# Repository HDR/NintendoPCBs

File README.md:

# [Make sure you read the License before downloading anything!](https://github.com/HDR/NintendoPCBs/blob/master/LICENSE)

# Please note that these boards can only be used to fix broken games, they can not be used for piracy/bootleg games

**All boards should be ordered in 0.8mm thickness with ENIG, Do not order in 1.6mm thickness or HASL!**

**AGB-E02-20:**

**AGB-E05-01:**

**DMG-KFDN-01:**

See the [Nintendo Board Scans](https://github.com/HDR/Nintendo_Board_Scans) for more.

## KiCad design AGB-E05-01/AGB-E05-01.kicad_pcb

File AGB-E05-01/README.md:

# AGB-E05-01

Intended as a replacement for Games like Emerald

## BOM
| **Designator** | **Part**                              |
|:-----------:|:-------------------------------------------------------------:|
| C1,C2,C3,C4 |                           100nF 0402                          |
|          C5 |            4pF or 10pF 0402 (depends on the board)            |
|    R1,R2,R3 |                          Unpopulated                          |
|    R4,R5,R9 |                            10K 0402                           |
|       R6,R7 |                           100K 0402                           |
|          R8 |                            1K 0402                            |
| R10         | 2K Resistor 0603 or 1uF Capacitor 0603 (depends on the board) |

### Images

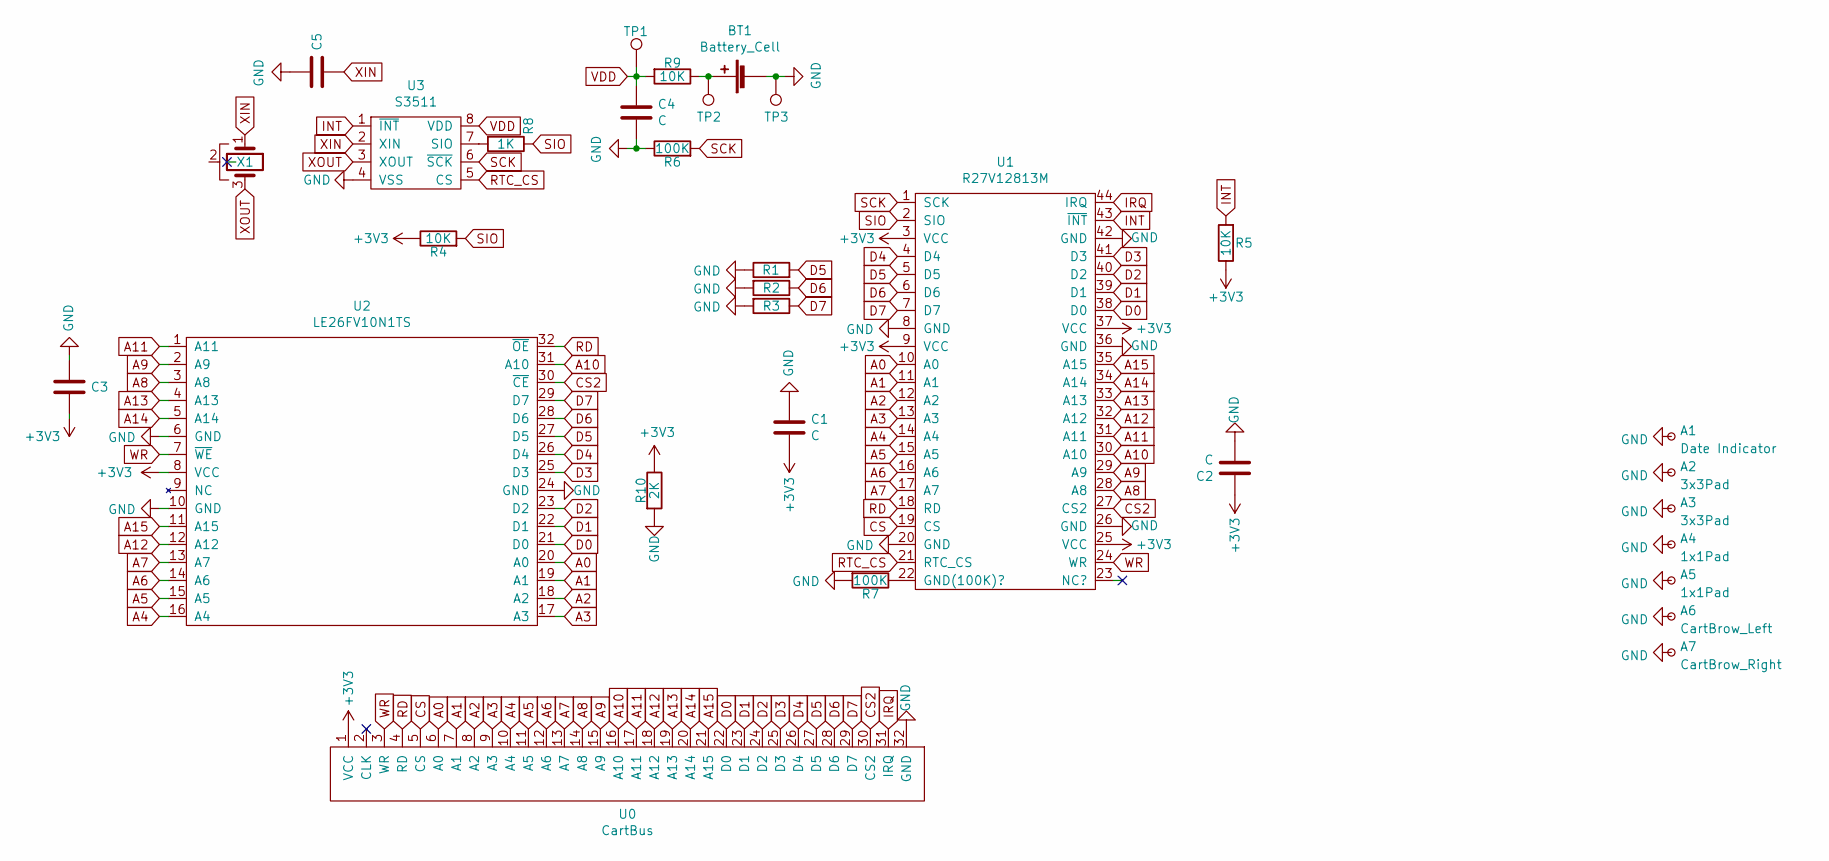
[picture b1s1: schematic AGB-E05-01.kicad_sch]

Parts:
A1: Date Indicator; 05 May
A2, A3: 3x3Pad; 3x3mm_Pad
A4, A5: 1x1Pad; 1x1mm_Pad
A6: CartBrow_Left; AGB-Cartbrow_Left
A7: CartBrow_Right; AGB-Cartbrow_Right
BT1: Battery_Cell; AGB-CR1616
C1, C2, C3, C4, C5: C; AGB-C_0402
R1, R2, R3: NC; AGB-R-0603_OPT
R4, R5, R9: 10K; AGB-R_0402
R6, R7: 100K; AGB-R_0402
R8: 1K; AGB-R_0402
R10: 2K; AGB-R-0603
TP1, TP2: TestPoint; AGB-Testpoint
TP3: TestPoint; AGB-Testpoint_Ground
U0: CartBus; AGB_Cartridge
U1: R27V12813M; AGB-TSOP-II-44_10.16x18.41mm_P0.8mm
U2: LE26FV10N1TS; AGB-TSOP-I-32
U3: S3511; AGB-SSOP8
X1: Crystal_GND2; AGB-Crystal

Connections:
+3V3: C1.1, C2.2, C3.1, R4.1, R5.1, R10.1, U0.1 (VCC), U1.3 (VCC), U1.9 (VCC), U1.25 (VCC), U1.37 (VCC), U2.8 (VCC)
A0: U0.6 (A0), U1.10 (A0), U2.20 (A0)
A1: U0.7 (A1), U1.11 (A1), U2.19 (A1)
A2: U0.8 (A2), U1.12 (A2), U2.18 (A2)
A3: U0.9 (A3), U1.13 (A3), U2.17 (A3)
A4: U0.10 (A4), U1.14 (A4), U2.16 (A4)
A5: U0.11 (A5), U1.15 (A5), U2.15 (A5)
A6: U0.12 (A6), U1.16 (A6), U2.14 (A6)
A7: U0.13 (A7), U1.17 (A7), U2.13 (A7)
A8: U0.14 (A8), U1.28 (A8), U2.3 (A8)
A9: U0.15 (A9), U1.29 (A9), U2.2 (A9)
A10: U0.16 (A10), U1.30 (A10), U2.31 (A10)
A11: U0.17 (A11), U1.31 (A11), U2.1 (A11)
A12: U0.18 (A12), U1.32 (A12), U2.12 (A12)
A13: U0.19 (A13), U1.33 (A13), U2.4 (A13)
A14: U0.20 (A14), U1.34 (A14), U2.5 (A14)
A15: U0.21 (A15), U1.35 (A15), U2.11 (A15)
CS: U0.5 (CS), U1.19 (CS)
CS2: U0.30 (CS2), U1.27 (CS2), U2.30 (~CE)
D0: U0.22 (D0), U1.38 (D0), U2.21 (D0)
D1: U0.23 (D1), U1.39 (D1), U2.22 (D1)
D2: U0.24 (D2), U1.40 (D2), U2.23 (D2)
D3: U0.25 (D3), U1.41 (D3), U2.25 (D3)
D4: U0.26 (D4), U1.4 (D4), U2.26 (D4)
D5: R1.2, U0.27 (D5), U1.5 (D5), U2.27 (D5)
D6: R2.1, U0.28 (D6), U1.6 (D6), U2.28 (D6)
D7: R3.1, U0.29 (D7), U1.7 (D7), U2.29 (D7)
GND: A1.1, A2.1, A3.1, A4.1, A5.1, A6.1, A7.1, BT1.2 (-), C1.2, C2.1, C3.2, C4.1, C5.1, R1.1, R2.2, R3.2, R6.1, R7.2, R10.2, TP3.1, U0.32 (GND), U1.8 (GND), U1.20 (GND), U1.26 (GND), U1.36 (GND), U1.42 (GND), U2.6 (GND), U2.10 (GND), U2.24 (GND), U3.4 (VSS); also elsewhere on the board
INT: R5.2, U1.43 (~INT), U3.1 (~INT)
IRQ: U0.31 (IRQ), U1.44 (IRQ)
unnamed: BT1.1 (+), R9.1, TP2.1
unnamed: R7.1, U1.22 (GND(100K)?)
unnamed: R8.2, U3.7 (SIO)
RD: U0.4 (RD), U1.18 (RD), U2.32 (~OE)
RTC_CS: U1.21 (RTC_CS), U3.5 (CS)
SCK: R6.2, U1.1 (SCK), U3.6 (~SCK)
SIO: R4.2, R8.1, U1.2 (SIO)
VDD: C4.2, R9.2, TP1.1, U3.8 (VDD)
WR: U0.3 (WR), U1.24 (WR), U2.7 (~WE)
XIN: C5.2, U3.2 (XIN), X1.1
XOUT: U3.3 (XOUT), X1.3

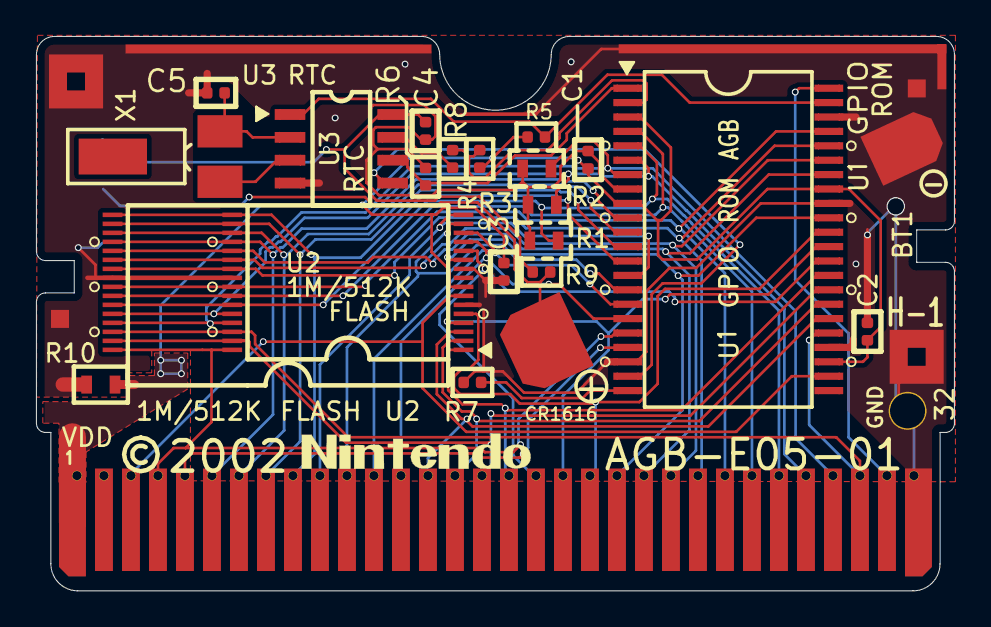
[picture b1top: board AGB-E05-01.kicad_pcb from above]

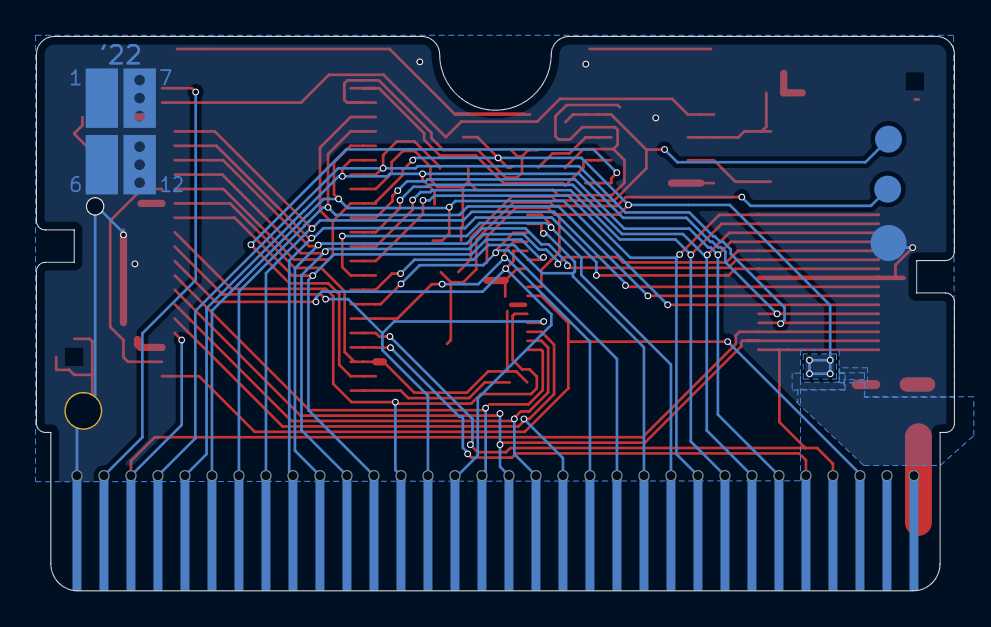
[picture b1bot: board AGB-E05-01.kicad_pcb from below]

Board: 2 copper layers, 51.0 x 30.8 mm, 36 parts (7 on the bottom side), 41 nets.

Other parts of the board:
G1: Nintendo Logo; Nintendo-GBA-Logo
PlatedHole1: MountingHole; TestPoint_Plated_Hole_D2.0mm
kibuzzard-62A1ACD3: G***; kibuzzard-62A1ACD3
kibuzzard-62A1AD16: G***; kibuzzard-62A1AD16
kibuzzard-62A1AD21: G***; kibuzzard-62A1AD21

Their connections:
GND: PlatedHole1.1; also elsewhere on the board

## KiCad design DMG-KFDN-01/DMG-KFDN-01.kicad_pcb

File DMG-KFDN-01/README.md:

# DMG-KFDN-01

Will be replaced with a better version in the coming weeks, please wait until then.

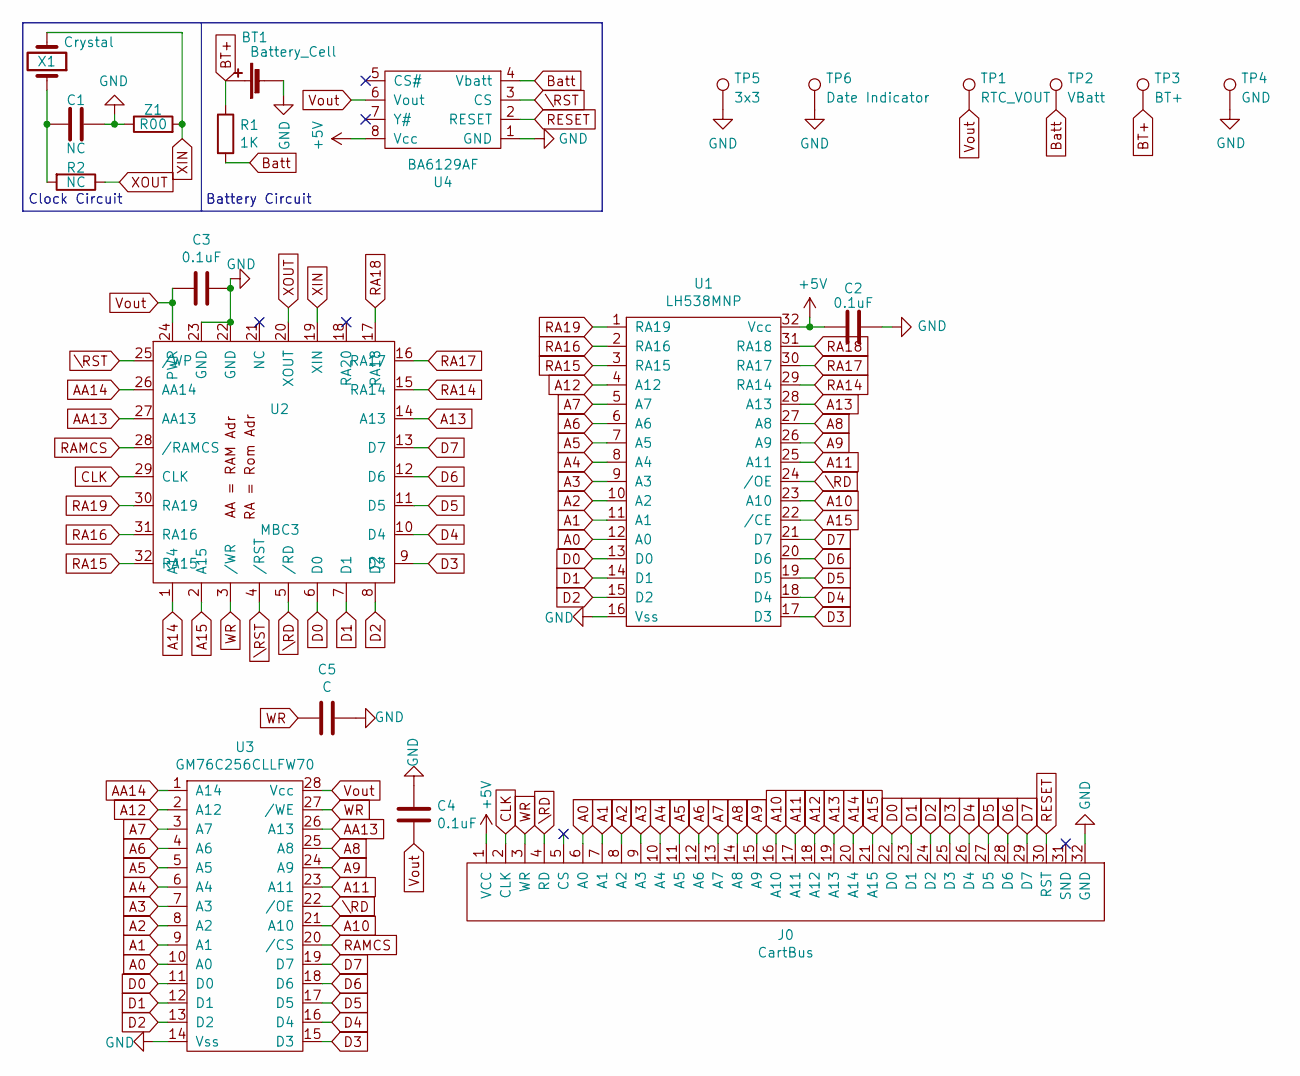
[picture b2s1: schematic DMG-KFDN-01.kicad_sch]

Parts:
BT1: Battery_Cell; CR2025_Tabbed
C1: NC; C_0805_2012Metric
C2, C3, C4: 0.1uF; C_0805_2012Metric
C5: C; C_0805_2012Metric
J0: CartBus; GB_Cartridge_Front_Only
R1: 1K; R_0805_2012Metric
R2: NC; R_0805_2012Metric
TP1: RTC_VOUT; GameBoy_Testpoint
TP2: VBatt; GameBoy_Testpoint
TP3: BT+; GameBoy_Testpoint
TP4: GND; GameBoy_Testpoint
TP5: 3x3; 3x3mm_Pad
TP6: Date Indicator; 12 December
U1: LH538MNP; SSOP-32_11.305x20.495mm_P1.27mm
U2: MBC3; LQFP-32_7x7mm_P0.8mm
U3: GM76C256CLLFW70; SOIC-28W_7.5x17.9mm_P1.27mm
U4: BA6129AF; SOIC-8_3.9x4.9mm_P1.27mm
X1: Crystal; Resonator_SMD_muRata_CDSCB-2pin_4.5x2.0mm_HandSoldering
Z1: R00; R_0805_2012Metric

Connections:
+5V: C2.1, J0.1 (VCC), U1.32 (Vcc), U4.8 (Vcc)
A0: J0.6 (A0), U1.12 (A0), U3.10 (A0)
A1: J0.7 (A1), U1.11 (A1), U3.9 (A1)
A2: J0.8 (A2), U1.10 (A2), U3.8 (A2)
A3: J0.9 (A3), U1.9 (A3), U3.7 (A3)
A4: J0.10 (A4), U1.8 (A4), U3.6 (A4)
A5: J0.11 (A5), U1.7 (A5), U3.5 (A5)
A6: J0.12 (A6), U1.6 (A6), U3.4 (A6)
A7: J0.13 (A7), U1.5 (A7), U3.3 (A7)
A8: J0.14 (A8), U1.27 (A8), U3.25 (A8)
A9: J0.15 (A9), U1.26 (A9), U3.24 (A9)
A10: J0.16 (A10), U1.23 (A10), U3.21 (A10)
A11: J0.17 (A11), U1.25 (A11), U3.23 (A11)
A12: J0.18 (A12), U1.4 (A12), U3.2 (A12)
A13: J0.19 (A13), U1.28 (A13), U2.14 (A13)
A14: J0.20 (A14), U2.1 (A14)
A15: J0.21 (A15), U1.22 (/CE), U2.2 (A15)
AA13: U2.27 (AA13), U3.26 (A13)
AA14: U2.26 (AA14), U3.1 (A14)
BT+: BT1.1 (+), R1.1, TP3.1; also elsewhere on the board
Batt: R1.2, TP2.1, U4.4 (Vbatt)
CLK: J0.2 (CLK~), U2.29 (CLK)
D0: J0.22 (D0), U1.13 (D0), U2.6 (D0), U3.11 (D0)
D1: J0.23 (D1), U1.14 (D1), U2.7 (D1), U3.12 (D1)
D2: J0.24 (D2), U1.15 (D2), U2.8 (D2), U3.13 (D2)
D3: J0.25 (D3), U1.17 (D3), U2.9 (D3), U3.15 (D3)
D4: J0.26 (D4), U1.18 (D4), U2.10 (D4), U3.16 (D4)
D5: J0.27 (D5), U1.19 (D5), U2.11 (D5), U3.17 (D5)
D6: J0.28 (D6), U1.20 (D6), U2.12 (D6), U3.18 (D6)
D7: J0.29 (D7), U1.21 (D7), U2.13 (D7), U3.19 (D7)
GND: BT1.2 (-), C1.2, C2.2, C3.2, C4.1, C5.1, J0.32 (GND), TP4.1, TP5.1, TP6.1, U1.16 (Vss), U2.22 (GND), U2.23 (GND), U3.14 (Vss), U4.1 (GND), Z1.1; also elsewhere on the board
unnamed: C1.1, R2.2, X1.1
RA14: U1.29 (RA14), U2.15 (RA14)
RA15: U1.3 (RA15), U2.32 (RA15)
RA16: U1.2 (RA16), U2.31 (RA16)
RA17: U1.30 (RA17), U2.16 (RA17)
RA18: U1.31 (RA18), U2.17 (RA18)
RA19: U1.1 (RA19), U2.30 (RA19)
RAMCS: U2.28 (/RAMCS), U3.20 (/CS)
RESET: J0.30 (RST), U4.2 (RESET)
Vout: C3.1, C4.2, TP1.1, U2.24 (PWR), U3.28 (Vcc), U4.6 (Vout)
WR: C5.2, J0.3 (WR), U2.3 (/WR), U3.27 (/WE)
XIN: U2.19 (XIN), X1.2, Z1.2
XOUT: R2.1, U2.20 (XOUT)
\RD: J0.4 (RD), U1.24 (/OE), U2.5 (/RD), U3.22 (/OE)
\RST: U2.4 (/RST), U2.25 (/WP), U4.3 (CS)

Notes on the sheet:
Battery Circuit
Clock Circuit

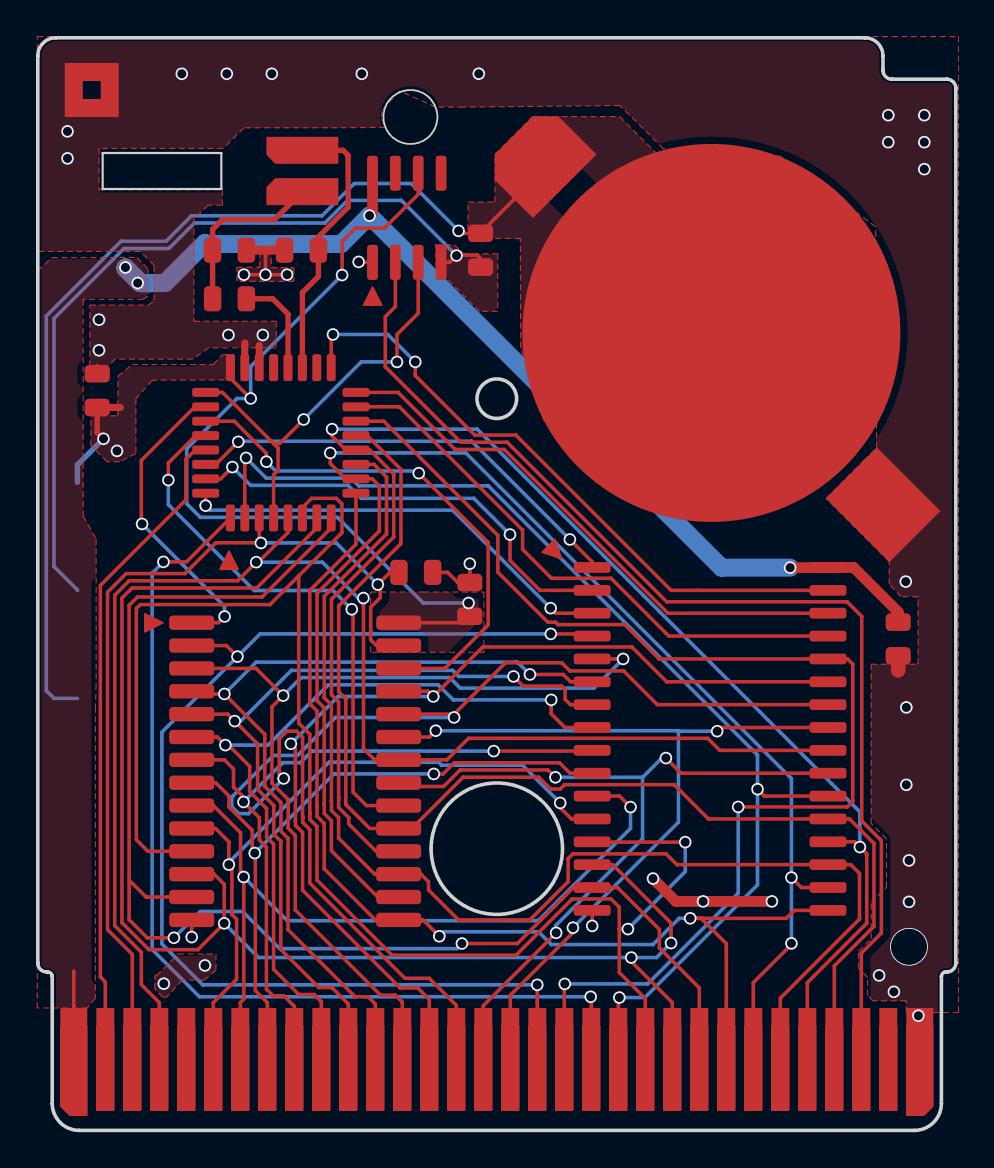
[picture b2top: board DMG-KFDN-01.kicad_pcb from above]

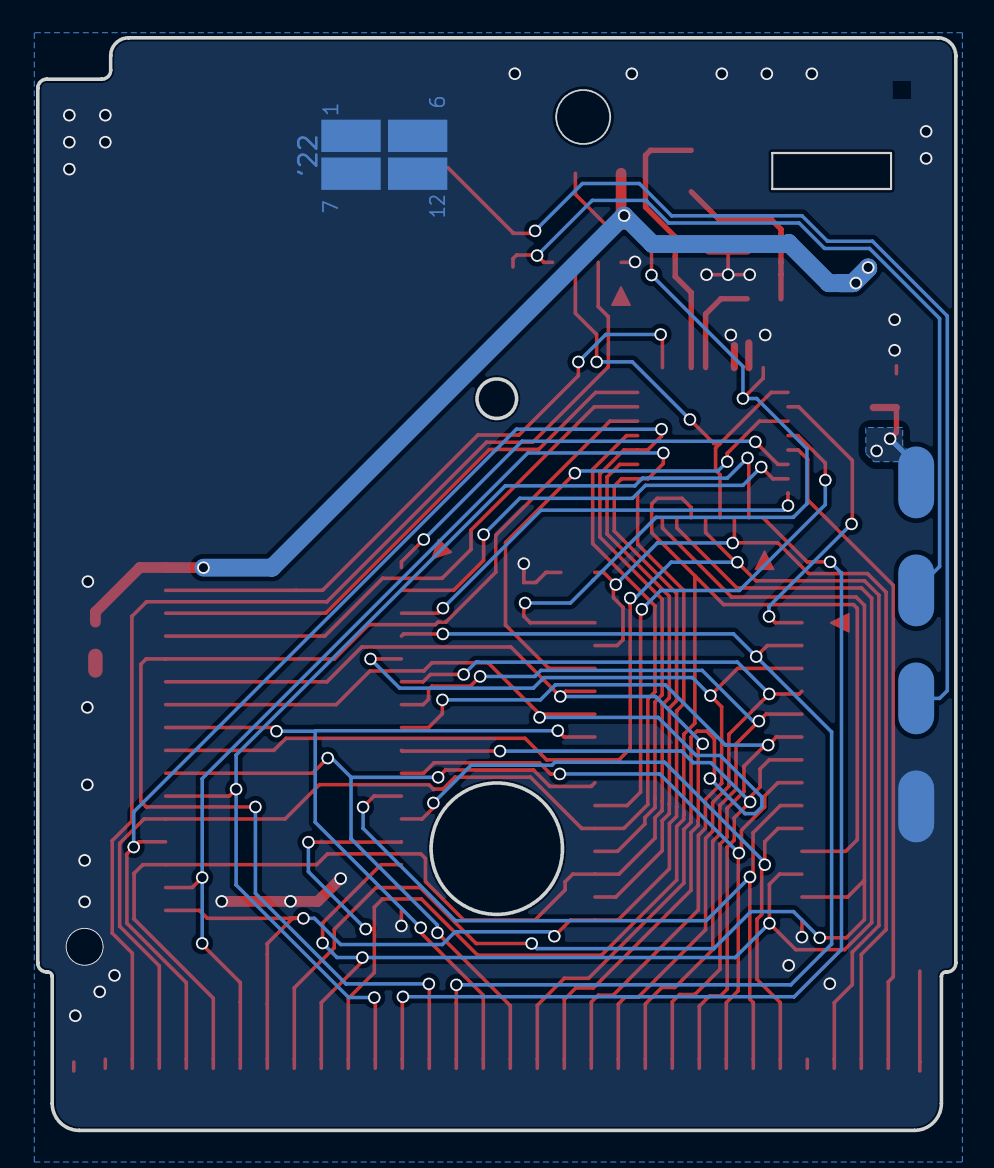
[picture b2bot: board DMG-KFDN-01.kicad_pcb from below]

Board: 2 copper layers, 51.0 x 60.7 mm, 21 parts (5 on the bottom side), 46 nets.

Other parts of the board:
Batt CR2025: Battery_Cell; CR2025_Tabbed

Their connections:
BT+: Batt CR2025.1 (+); also elsewhere on the board
GND: Batt CR2025.2 (-); also elsewhere on the board

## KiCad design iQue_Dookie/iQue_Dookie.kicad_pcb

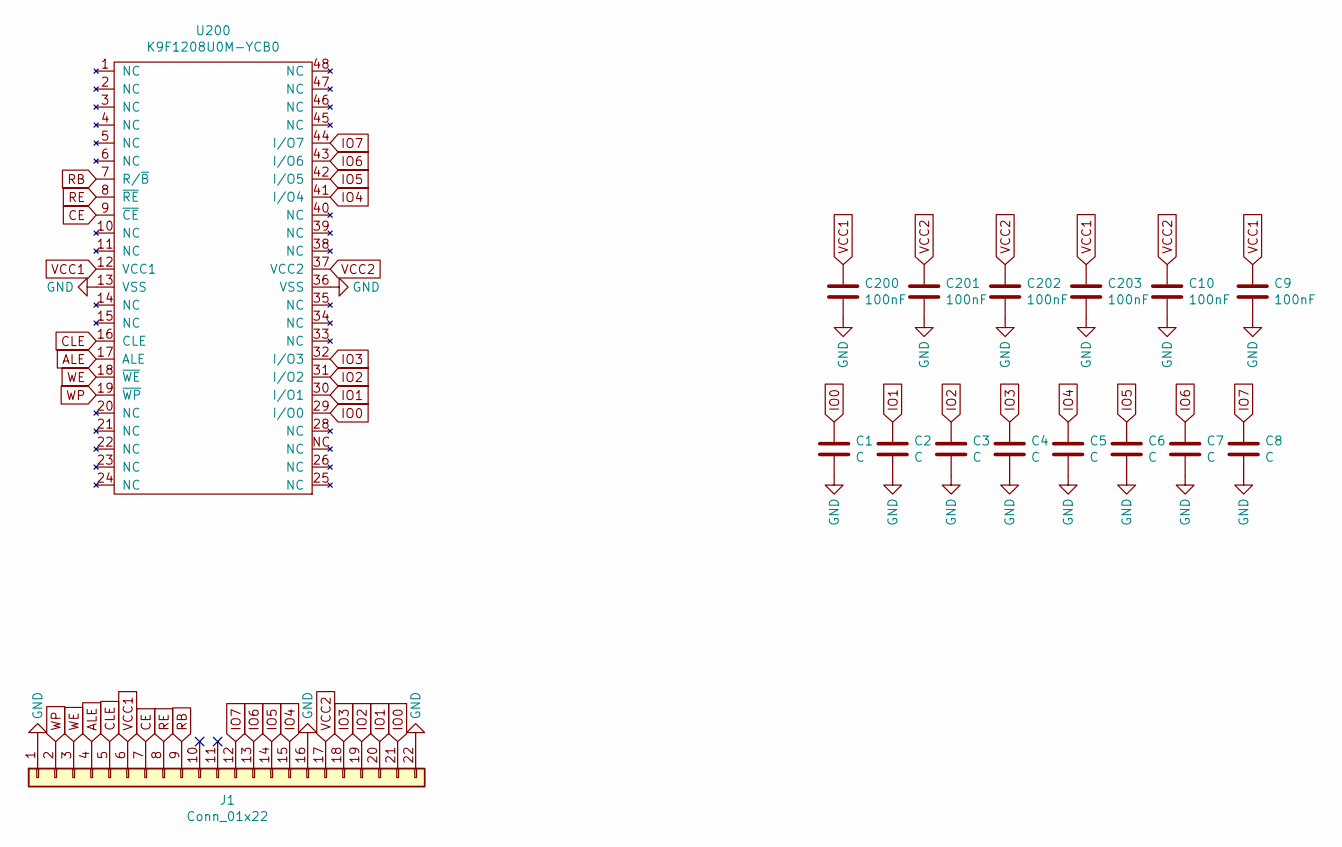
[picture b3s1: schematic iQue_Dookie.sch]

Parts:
C1, C2, C3, C4, C5, C6, C7, C8: C; C_0402_1005Metric
C9, C10, C200, C201, C202, C203: 100nF; C_0402_1005Metric
J1: Conn_01x22; iQue_Dookie_CartBus
U200: K9F1208U0M-YCB0; TSOP-I-48_18.4x12mm_P0.5mm

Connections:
ALE: J1.4, U200.17 (ALE); also elsewhere on the board
CE: J1.7, U200.9 (~CE); also elsewhere on the board
CLE: J1.5, U200.16 (CLE); also elsewhere on the board
GND: C1.2, C2.2, C3.2, C4.2, C5.2, C6.2, C7.2, C8.2, C9.2, C10.2, C200.2, C201.2, C202.2, C203.2, J1.1, J1.16, J1.22, U200.13 (VSS), U200.36 (VSS); also elsewhere on the board
IO0: C1.1, J1.21, U200.29 (I/O0); also elsewhere on the board
IO1: C2.1, J1.20, U200.30 (I/O1); also elsewhere on the board
IO2: C3.1, J1.19, U200.31 (I/O2); also elsewhere on the board
IO3: C4.1, J1.18, U200.32 (I/O3); also elsewhere on the board
IO4: C5.1, J1.15, U200.41 (I/O4); also elsewhere on the board
IO5: C6.1, J1.14, U200.42 (I/O5); also elsewhere on the board
IO6: C7.1, J1.13, U200.43 (I/O6); also elsewhere on the board
IO7: C8.1, J1.12, U200.44 (I/O7); also elsewhere on the board
RB: J1.9, U200.7 (R/~B); also elsewhere on the board
RE: J1.8, U200.8 (~RE); also elsewhere on the board
VCC1: C9.1, C200.1, C203.1, J1.6, U200.12 (VCC1); also elsewhere on the board
VCC2: C10.1, C201.1, C202.1, J1.17, U200.37 (VCC2); also elsewhere on the board
WE: J1.3, U200.18 (~WE); also elsewhere on the board
WP: J1.2, U200.19 (~WP); also elsewhere on the board

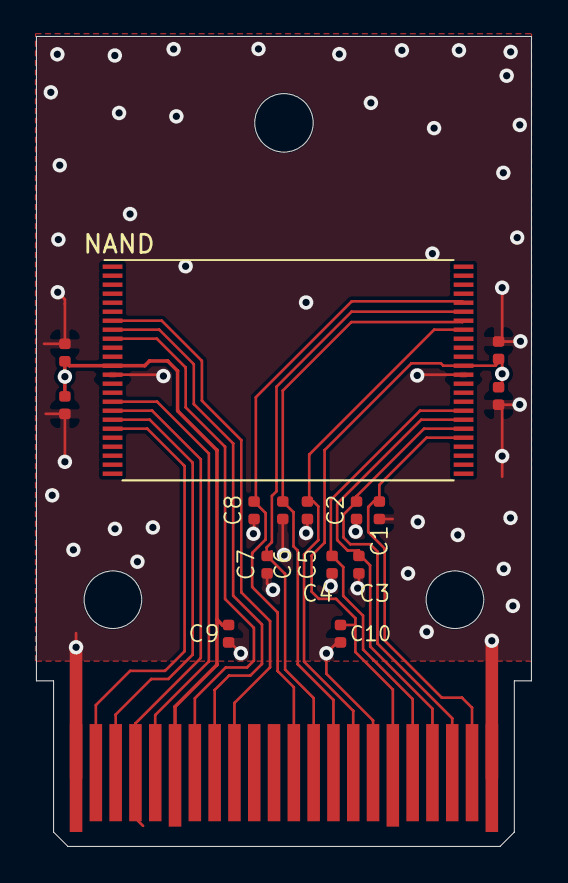
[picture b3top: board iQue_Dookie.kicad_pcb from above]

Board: 2 copper layers, 27.5 x 45.0 mm, 16 parts (0 on the bottom side), 18 nets.

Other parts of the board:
NAND: K9F1208U0M-YCB0; TSOP-I-48_18.4x12mm_P0.5mm

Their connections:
ALE: NAND.17; also elsewhere on the board
CE: NAND.9; also elsewhere on the board
CLE: NAND.16; also elsewhere on the board
GND: NAND.13, NAND.36; also elsewhere on the board
IO0: NAND.29; also elsewhere on the board
IO1: NAND.30; also elsewhere on the board
IO2: NAND.31; also elsewhere on the board
IO3: NAND.32; also elsewhere on the board
IO4: NAND.41; also elsewhere on the board
IO5: NAND.42; also elsewhere on the board
IO6: NAND.43; also elsewhere on the board
IO7: NAND.44; also elsewhere on the board
RB: NAND.7; also elsewhere on the board
RE: NAND.8; also elsewhere on the board
VCC1: NAND.12; also elsewhere on the board
VCC2: NAND.37; also elsewhere on the board
WE: NAND.18; also elsewhere on the board
WP: NAND.19; also elsewhere on the board

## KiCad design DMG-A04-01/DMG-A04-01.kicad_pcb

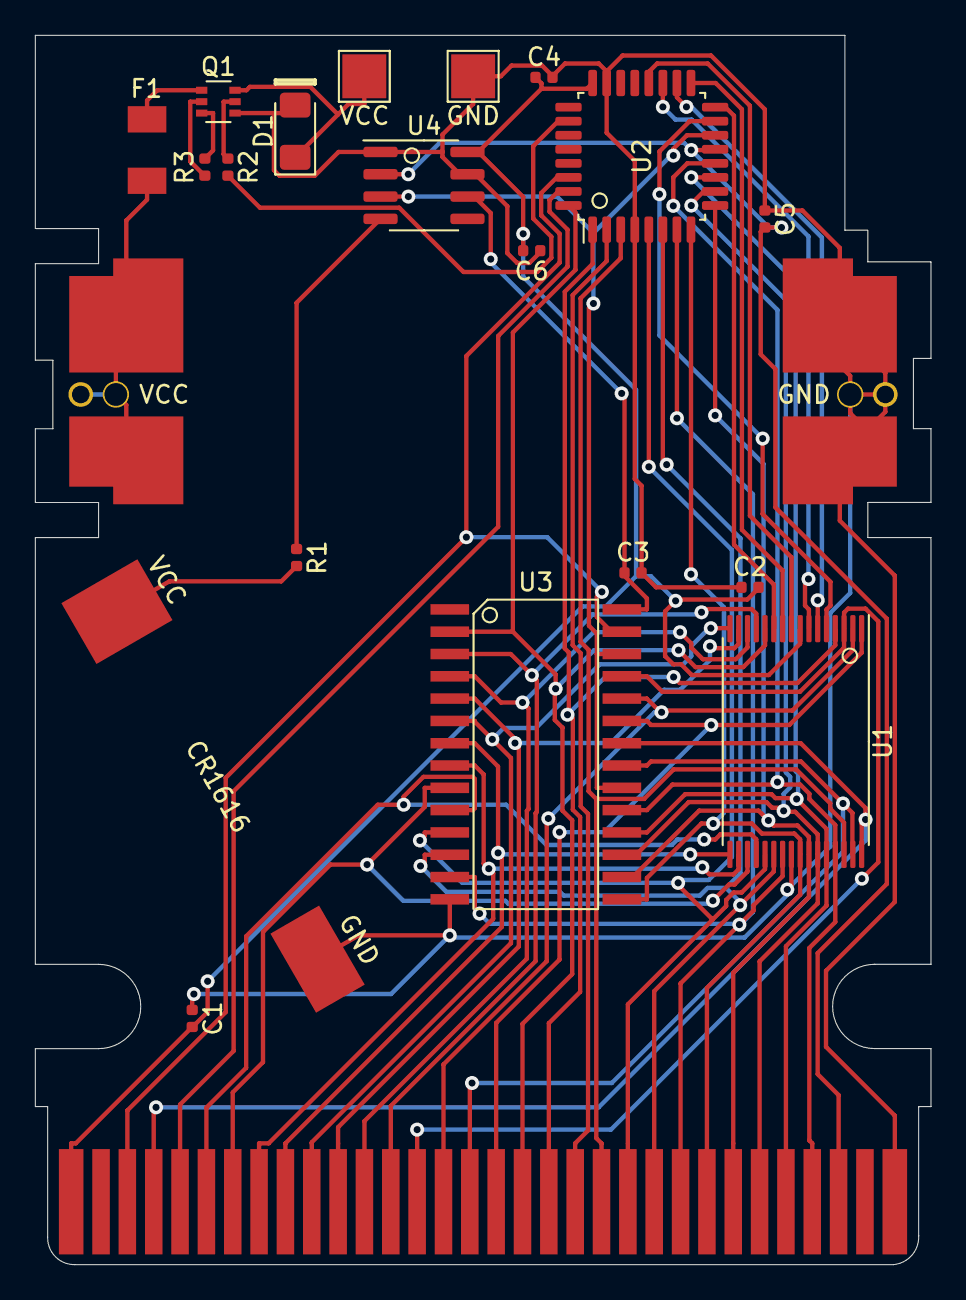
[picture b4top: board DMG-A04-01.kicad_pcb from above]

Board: 2 copper layers, 51.0 x 70.0 mm, 22 parts (0 on the bottom side), 47 nets.

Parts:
C1, C2, C3, C4, C6: C; C_0402_1005Metric
C5: NC; C_0402_1005Metric
CR1616: CR1616; CR1616-DMG
D1: D; D_1206_3216Metric_Pad1.42x1.75mm_HandSolder
F1: 10; DMG-A04-01_Fuse
GND: AAA GND; DMG-A04-01_BAT2-Negative
GND#2: Motor GND; TestPoint_Pad_2.5x2.5mm
Q1: PNP Transistor; DMG-A04-01-Q1
R1: 10K; R_0402_1005Metric
R2: 30K; R_0402_1005Metric
R3: 390; R_0402_1005Metric
U0: CartBus; GBBus
U1: MX23C8006-12; TSOP-I-32_11.8x8mm_P0.5mm
U2: MBC5; LQFP-32_7x7mm_P0.8mm
U3: HY6264A
U4: MM1134A; SOIC-8_3.9x4.9mm_P1.27mm
VCC: AAA Positive; DMG-A04-01_BAT2-Positive
VCC#2: Motor VCC; TestPoint_Pad_2.5x2.5mm

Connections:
+5V: C1.2, C2.2, C4.1, C6.2, U0.1, U1.8, U2.24, U4.8
A0: U0.6, U1.20, U3.10
A1: U0.7, U1.19, U3.9
A2: U0.8, U1.18, U3.8
A3: U0.9, U1.17, U3.7
A4: U0.10, U1.16, U3.6
A5: U0.11, U1.15, U3.5
A6: U0.12, U1.14, U3.4
A7: U0.13, U1.13, U3.3
A8: U0.14, U1.3, U3.25
A9: U0.15, U1.2, U3.24
A10: U0.16, U1.31, U3.21
A11: U0.17, U1.1, U3.23
A12: U0.18, U1.12, U2.32, U3.2
A13: U0.19, U1.4, U2.1
A14: U0.20, U2.2
A15: U0.21, U1.30, U2.3
AA16: R2.2, U2.26
CS: U0.5, U2.31
D0: U0.22, U1.21, U2.5, U3.11
D1: U0.23, U1.22, U2.6, U3.12
D2: U0.24, U1.23, U2.7, U3.13
D3: U0.25, U1.25, U2.8, U3.15
D4: U0.26, U1.26, U2.9, U3.16
D5: U0.27, U1.27, U2.10, U3.17
D6: U0.28, U1.28, U2.11, U3.18
D7: U0.29, U1.29, U2.12, U3.19
GND: C1.1, C2.1, C3.2, C4.2, C5.1, C6.1, CR1616.2, D1.2, GND.1, GND#2.1, Q1.4, U0.32, U1.24, U2.4, U2.23, U3.14, U4.1, U4.7
unnamed: CR1616.1, R1.2
unnamed: F1.1, VCC.1
unnamed: D1.1, Q1.6, VCC#2.1
unnamed: F1.2, Q1.1
unnamed: Q1.2, R3.1
unnamed: Q1.3, R3.2
unnamed: Q1.5, R2.1
unnamed: R1.1, U4.4
RA14: U1.5, U2.15
RA15: U1.11, U2.16
RA16: U1.10, U2.17
RA17: U1.6, U2.18
RA18: U1.7, U2.19
RA19: U1.9, U2.20
RAMCS: U2.14, U3.20, U3.26, U4.3
RESET: C5.2, U0.30, U2.13, U4.2
RamVcc: C3.1, U3.28, U4.6
WR: U0.3, U2.30, U3.27
\RD: U0.4, U1.32, U3.22

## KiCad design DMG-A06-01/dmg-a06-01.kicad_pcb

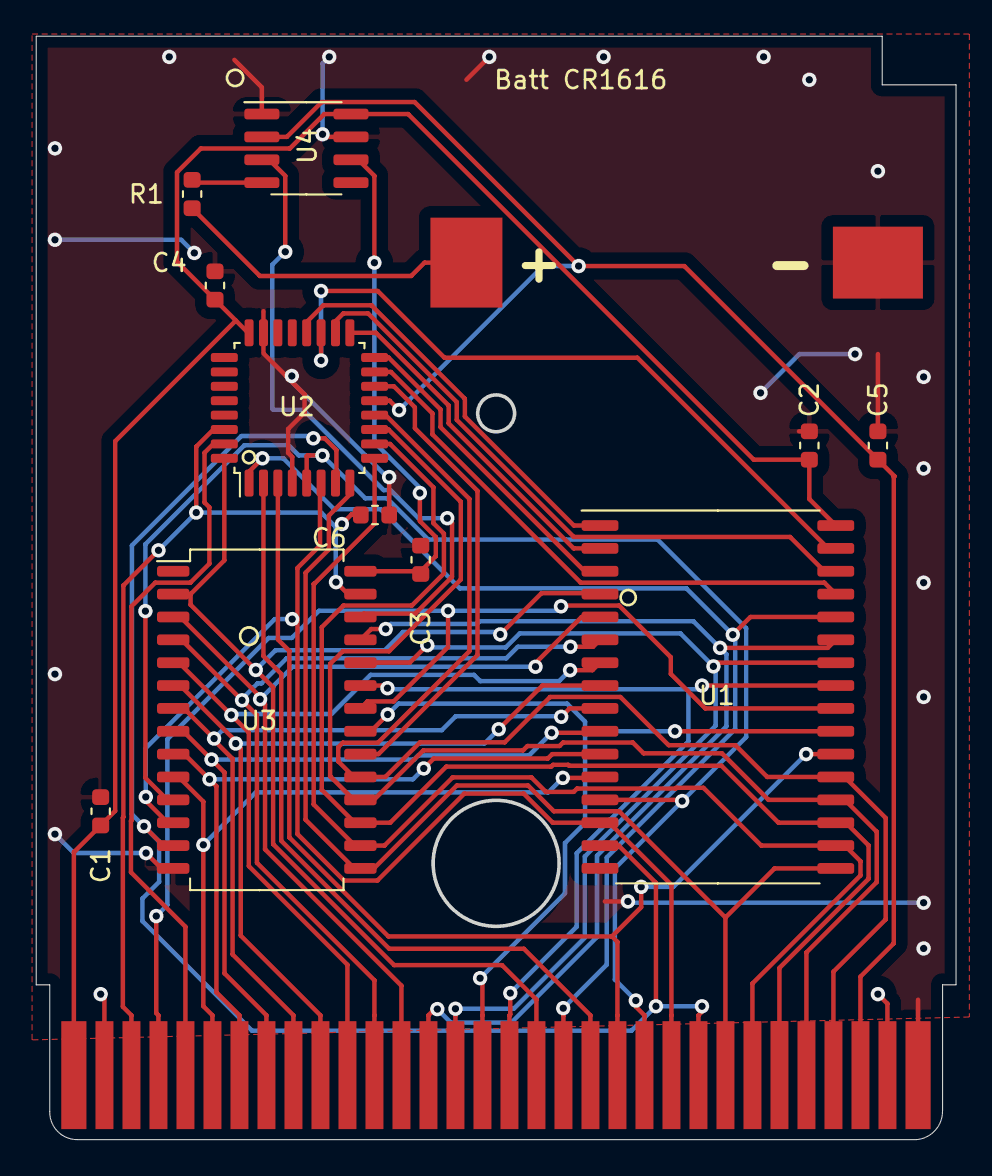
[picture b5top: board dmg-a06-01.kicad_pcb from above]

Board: 2 copper layers, 50.9 x 61.1 mm, 13 parts (0 on the bottom side), 41 nets.

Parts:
Batt CR1616: Battery_Cell; CR2025
C1: NC; C_0603_1608Metric
C2, C3, C4, C6: 0.1uF; C_0603_1608Metric
C5: C; C_0603_1608Metric
R1: NC; R_0603_1608Metric
U0: CartBus
U1: LH538MNP; SSOP-32_11.305x20.495mm_P1.27mm
U2: MBC5; LQFP-32_7x7mm_P0.8mm
U3: GM76C256CLLFW70
U4: BA6129AF; SOIC-8_3.9x4.9mm_P1.27mm

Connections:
+5V: C1.1, C2.2, C4.2, U0.1, U1.32, U2.24, U4.8
A0: U0.6, U1.12, U3.10
A1: U0.7, U1.11, U3.9
A2: U0.8, U1.10, U3.8
A3: U0.9, U1.9, U3.7
A4: U0.10, U1.8, U3.6
A5: U0.11, U1.7, U3.5
A6: U0.12, U1.6, U3.4
A7: U0.13, U1.5, U3.3
A8: U0.14, U1.27, U3.25
A9: U0.15, U1.26, U3.24
A10: U0.16, U1.23, U3.21
A11: U0.17, U1.25, U3.23
A12: U0.18, U1.4, U2.32, U3.2
A13: U0.19, U1.28, U2.1
A14: U0.20, U2.2
A15: U0.21, U1.22, U2.3
AA13: U3.26, U4.3
Batt: R1.2, U4.4
D0: U0.22, U1.13, U2.5, U3.11
D1: U0.23, U1.14, U2.6, U3.12
D2: U0.24, U1.15, U2.7, U3.13
D3: U0.25, U1.17, U2.8, U3.15
D4: U0.26, U1.18, U2.9, U3.16
D5: U0.27, U1.19, U2.10, U3.17
D6: U0.28, U1.20, U2.11, U3.18
D7: U0.29, U1.21, U2.12, U3.19
GND: Batt CR1616.2, C1.2, C2.1, C3.2, C4.1, C5.2, C6.2, U0.32, U1.16, U2.4, U2.23, U3.14, U4.1, U4.7
unnamed: Batt CR1616.1, R1.1
unnamed: U0.5, U2.31
RA14: U1.29, U2.15
RA15: U1.3, U2.16
RA16: U1.2, U2.17
RA17: U1.30, U2.18
RAMCS: U2.14, U3.20
RESET: C5.1, U0.30, U2.13, U4.2
Vout: C3.1, U3.28, U4.6
WR: C6.1, U0.3, U2.30, U3.27
XIN: U1.31, U2.19
XOUT: U1.1, U2.20
\RD: U0.4, U1.24, U3.22

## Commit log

2019-10-14 DMG-KFDN-01
2019-10-14 Create LICENSE
2019-10-14 Add Gerber
2019-10-19 Add AGB-E05-01
    Added AGB-E05-01, this is a board mainly for Pokemon Ruby, Sapphire and
    Emerald
2019-10-19 Add gerbers for AGB-E05-01
2019-11-14 Move R7 and R10 up
2019-11-14 Move battery pads slightly up
2019-11-16 Update AGB-E05-01
    Moved bottom of screwpost cutout down slightly for better alignment,
    moved all components up to make the pcb fit like it should inside the
    original shell
2019-11-29 Added DMG-A04-01
    Added DMG-A04-01 (Pokemon Pinball), keep in mind this board is untested
2019-12-22 Added AGB-E02-20
    AGB-E02-20 supports Fire Red and Leaf Green
2020-03-31 Added DMG-A06-01 board
2020-03-31 Added .pro and gerber files for DMG-A06-01
2020-08-18 Update AGB-E02-20
    AGB-E02-20 looks much more "OEM" now
2020-10-16 Update AGB-E02-20
    AGB-E02-20 is now mostly identical to the original pcb (this was a lot of work)
2021-06-14 add the iQue "Dookie"
2022-04-03 Fix issues with DMG-KFDN-01 (see #4)
2022-06-20 Updated AGB-E05-01 to look more original
2022-08-21 KDFN -> KFDN (silkscr typo)
2022-08-22 Updated KFDN gerbers
2022-12-27 Start updating readmes
2023-01-16 Add AGB-E02-20 OpenBoardView file
2023-03-05 Update AGB-E02-20
    1 to 1 traces
    KiCad 7
2023-03-23 Created version 1.1 of DMG-A06-01 replacement PCB
2023-03-31 Update DMG-KFDN-01
2023-03-31 Move images
2023-07-09 docs: Fix incorrect/missing R9 designator
    R6 was listed twice, and R9 was missing. I believe that the second R6 was a typo. Confirmed with a multimeter that R9 was 10K.
2024-10-08 Remove copyrighted logo
2024-10-08 Remove logos
2024-10-08 Remove logos
    removes logos for copyright reasons
2024-10-08 Fix missing traces
2025-02-12 Corrected boardview orientation for AGB-E02-20
    Corrected the boardview file for the AGB-E02-20 board which was mirrored and upside down.
2026-01-08 Fix AGB-E05-01 Kicad PCB File
    Fixes missing traces from AGB-E05-01.kicad_pcb
2026-01-08 Update AGB-05-01 Kicad files
    Upgrade to kicad 9.0
